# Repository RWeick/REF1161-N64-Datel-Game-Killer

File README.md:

# REF1161-N64-Datel-Game-Killer
The extracted N64 game saves, Kicad Schematic, and PCB files for the Datel Game Killer for the N64.

This product overwrites targeted portions of the game save for the selected game to yield a modified game with hacks enabled. It does not upload a full game save to the attached game.

The game saves presented in this repository were clean before being modified by the Game Killer, so they only contain the Game Killer modifications.

The Pilot Wings 64 save only seems to work with the PAL version of the game. The rest appear to work with their NTSC counterparts as well as the PAL games they were designed for.

More information here: https://www.nesworld.com/article.php?system=n64&data=n64-gamekiller

PCB Thickness: 1.2 mm

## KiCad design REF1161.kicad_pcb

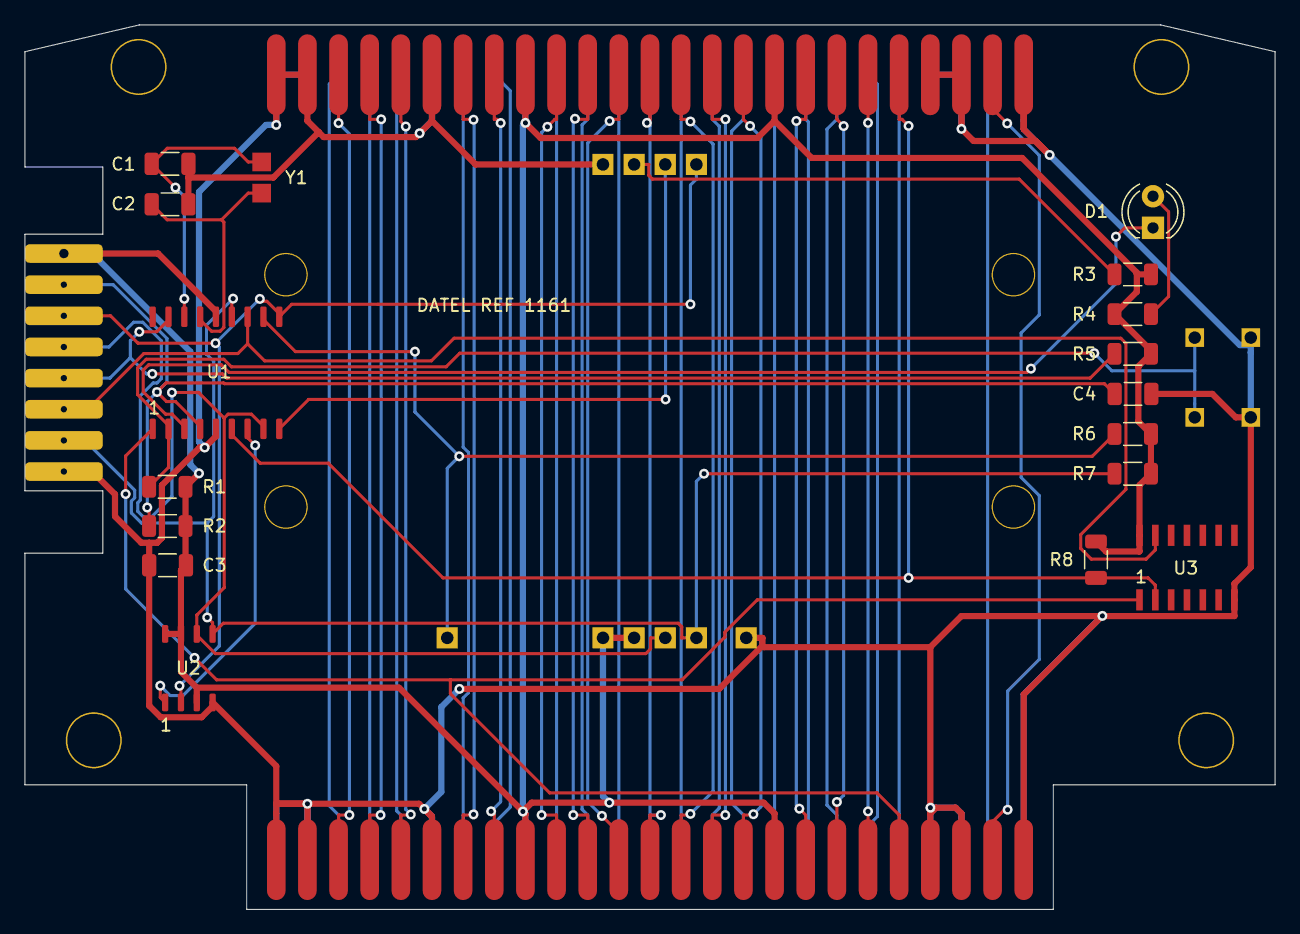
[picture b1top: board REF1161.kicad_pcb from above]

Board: 2 copper layers, 100.3 x 71.0 mm, 26 parts (0 on the bottom side), 52 nets.

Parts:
C1, C2: 15 pF; C_1206_3216Metric
C3, C4: 100 nF; C_1206_3216Metric
D1: LED; LED_D4.0mm
Hole1, Hole2, Hole3, Hole4: N64-Hole
J1: Cartridge Slot; Cart Edge Connector
J2: Cartridge Edge Connector; Cart Edge Connector
J3: PIC Edge Pads; PIC Edge Connector
J4: Smart_Card_Reader; Smart Card
R1, R2, R3, R5, R6, R7, R8: 10K Ohm; R_1206_3216Metric
R4: 220 Ohm; R_1206_3216Metric
SW1: SW_Push_Dual; 1cm Push Button
U1: PIC 16C558
U2: Unknown SOIC8
U3: 74HC4066D; 74HC4066
Y1: 20 MHz; 20MHz Crystal

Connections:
/12V: J1.13 (12V), J1.38 (12V), J2.13 (12V), J2.38 (12V)
/AD0: J1.28 (AD0), J2.28 (AD0)
/AD1: J1.29 (AD1), J2.29 (AD1)
/AD2: J1.30 (AD2), J2.30 (AD2)
/AD3: J1.32 (AD3), J2.32 (AD3)
/AD4: J1.36 (AD4), J2.36 (AD4)
/AD5: J1.37 (AD5), J2.37 (AD5)
/AD6: J1.40 (AD6), J2.40 (AD6)
/AD7: J1.41 (AD7), J2.41 (AD7)
/AD8: J1.16 (AD8), J2.16 (AD8)
/AD9: J1.15 (AD9), J2.15 (AD9)
/AD10: J1.12 (AD10), J2.12 (AD10)
/AD11: J1.11 (AD11), J2.11 (AD11)
/AD12: J1.7 (AD12), J2.7 (AD12)
/AD13: J1.5 (AD13), J2.5 (AD13)
/AD14: J1.4 (AD14), J2.4 (AD14)
/AD15: J1.3 (AD15), J2.3 (AD15)
/ALE_H: J1.35 (ALE_H), J2.35 (ALE_H)
/ALE_L: J1.33 (ALE_L), J2.33 (ALE_L)
/Button: R1.1, SW1.1, U1.2 (RA3)
/CIC_11: J1.19 (CIC_11), J2.19 (CIC_11)
/CIC_14: J1.43 (CIC_14), J2.43 (CIC_14)
/CIC_15: J1.18 (CIC_15), J2.18 (CIC_15)
/GND: C1.2, C2.2, C3.1, C4.2, J1.1 (GND), J1.2 (GND), J1.6 (GND), J1.22 (GND), J1.23 (GND), J1.25 (GND), J1.26 (GND), J1.27 (GND), J1.31 (GND), J1.47 (GND), J1.48 (GND), J1.50 (GND), J2.1 (GND), J2.2 (GND), J2.6 (GND), J2.22 (GND), J2.23 (GND), J2.25 (GND), J2.26 (GND), J2.27 (GND), J2.31 (GND), J2.47 (GND), J2.48 (GND), J2.50 (GND), J3.8, J4.5 (GND), J4.9 (CD1), SW1.2, U1.5 (VSS), U2.4 (GND), U3.7 (GND)
/INT1: J1.44 (/INT1), J2.44 (/INT1)
/LAUDIO: J1.24 (LAUDIO), J2.24 (LAUDIO)
/LED: D1.1 (K), U1.3 (RA4/TOCKI)
/MCLR.VPP: C4.1, J3.2, R2.1, U1.4 (MCLR/Vpp)
/NMI: J1.45 (/NMI), J2.45 (/NMI)
/RA0: J3.5, R5.1, U1.17 (RA0)
/RAUDIO: J1.49 (RAUDIO), J2.49 (RAUDIO)
/RB1: U1.7 (RB1), U2.1 (I/O)
/SC.CD2: J4.10 (CD2), R6.1, U1.11 (RB5)
/SC.CLK: J3.4, J4.3 (CLK), U1.8 (RB2), U2.6 (I/O)
/SC.I/O: J4.7 (I/O), U1.9 (RB3)
/SC.Pin4: J3.7, J4.4 (App_Specific), R7.1, U1.13 (RB7), U2.5 (I/O)
/SC.Pin8: J3.3, J4.8 (App_Specific), U1.10 (RB4), U2.2 (I/O)
/SC.VPP: J4.6 (VPP), R3.1
/S_DAT.Bottom: J2.21 (EEPROM_DAT), U1.1 (RA2), U3.1 (1Y)
/S_DAT.Top: J1.21 (EEPROM_DAT), R8.1, U1.6 (RB0/INT), U3.2 (1Z)
/Switch: J3.6, U1.12 (RB6), U3.13 (1E)
/UNUSED_Front: J1.14 (12V), J2.14 (12V)
/UNUSED_Rear: J1.39 (12V), J2.39 (12V)
/VCC: C3.2, J1.9 (3.3V), J1.17 (3.3V), J1.34 (3.3V), J2.9 (3.3V), J2.17 (3.3V), J2.34 (3.3V), J3.1, J4.1 (VCC), J4.2 (RST), R1.2, R2.2, R3.2, R4.1, R5.2, R6.2, R7.2, R8.2, U1.14 (VDD), U2.3 (VCC), U2.7 (VCC), U2.8 (VCC), U3.14 (VCC)
/VCC.Odd: J1.42 (3.3V), J2.42 (3.3V)
/Video_Sync: J1.46 (VIDEO_SYNC), J2.46 (VIDEO_SYNC)
//COLD_RESET: J1.20 (/ColdReset), J2.20 (/ColdReset)
//Read: J1.10 (/RD), J2.10 (/RD)
//Write: J1.8 (/WR), J2.8 (/WR)
unnamed: D1.2 (A), R4.2
unnamed: C1.1, U1.16 (OSC1/CLKIN), Y1.2
unnamed: C2.1, U1.15 (OSC2/CLKOUT), Y1.1
